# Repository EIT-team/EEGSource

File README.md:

# EEGSource
Generate EEG signals for saline phantoms

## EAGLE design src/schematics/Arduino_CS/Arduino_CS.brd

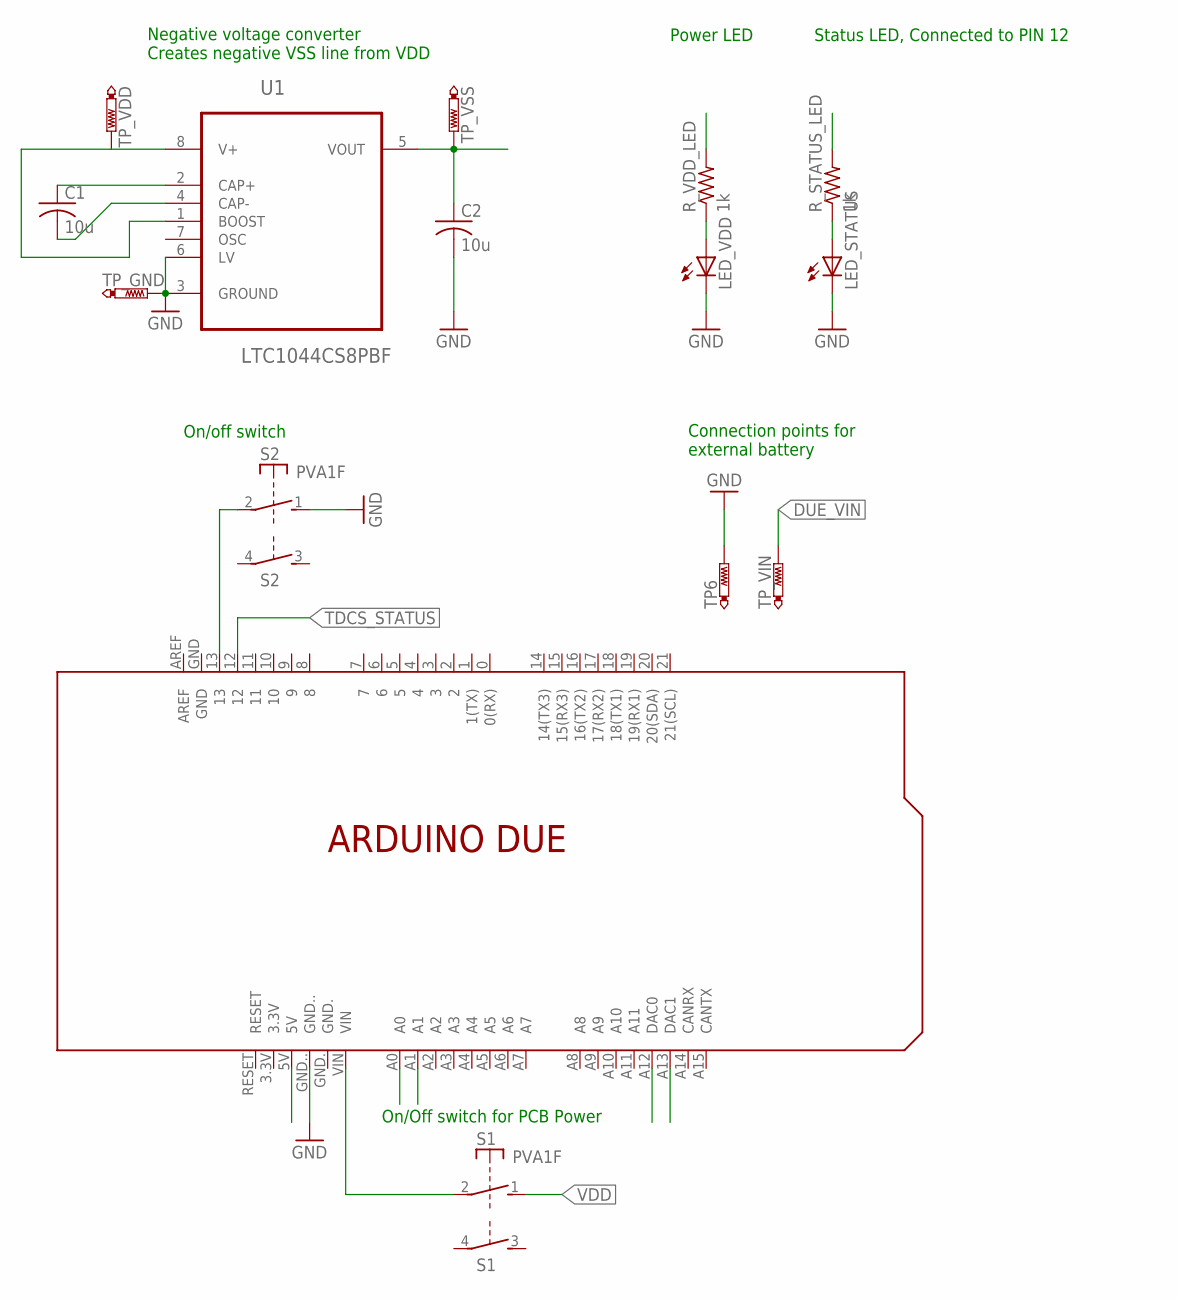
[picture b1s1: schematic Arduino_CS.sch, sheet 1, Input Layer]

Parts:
C1, C2: 10u; C0805
LED_STATUS: LEDSML0805; SML0805
LED_VDD: LEDSML0805; SML0805
PCB1: ARDUINO_DUE
R_STATUS_LED: 1k; M0805
R_VDD_LED: 1k; M0805
S1, S2: PVA1F
TP6: PTR1PAD1-13; P1-13
TP_GND: PTR1PAD1-13; P1-13
TP_VDD: PTR1PAD1-13; P1-13
TP_VIN: PTR1PAD1-13; P1-13
TP_VSS: PTR1PAD1-13; P1-13
U1: LTC1044CS8PBF; SOIC127P600X175-8N

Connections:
A0: PCB1.A0; also elsewhere on the board
A1: PCB1.A1
DAC0: PCB1.A12 (DAC0); also elsewhere on the board
DAC1: PCB1.A13 (DAC1)
DUE_5V: PCB1.5V; also elsewhere on the board
DUE_VIN: PCB1.VIN, S1.2, TP_VIN.TP
GND: C2.2, LED_STATUS.C, LED_VDD.C, PCB1.GND.., S2.1 (S), TP6.TP, TP_GND.TP, U1.3 (GROUND), U1.6 (LV); also elsewhere on the board
unnamed: PCB1.13, S2.2
unnamed: C1.1, U1.2 (CAP+)
unnamed: C1.2, U1.4 (CAP-)
unnamed: LED_STATUS.A, R_STATUS_LED.1
unnamed: LED_VDD.A, R_VDD_LED.1
TDCS_STATUS: PCB1.12, R_STATUS_LED.2
VDD: R_VDD_LED.2, S1.1 (S), TP_VDD.TP, U1.1 (BOOST), U1.8 (V+); also elsewhere on the board
VSS: C2.1, TP_VSS.TP, U1.5 (VOUT); also elsewhere on the board

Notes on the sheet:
Power LED
Status LED, Connected to PIN 12
Negative voltage converter Creates negative VSS line from VDD
On/off switch
On/Off switch for PCB Power
Connection points for external battery

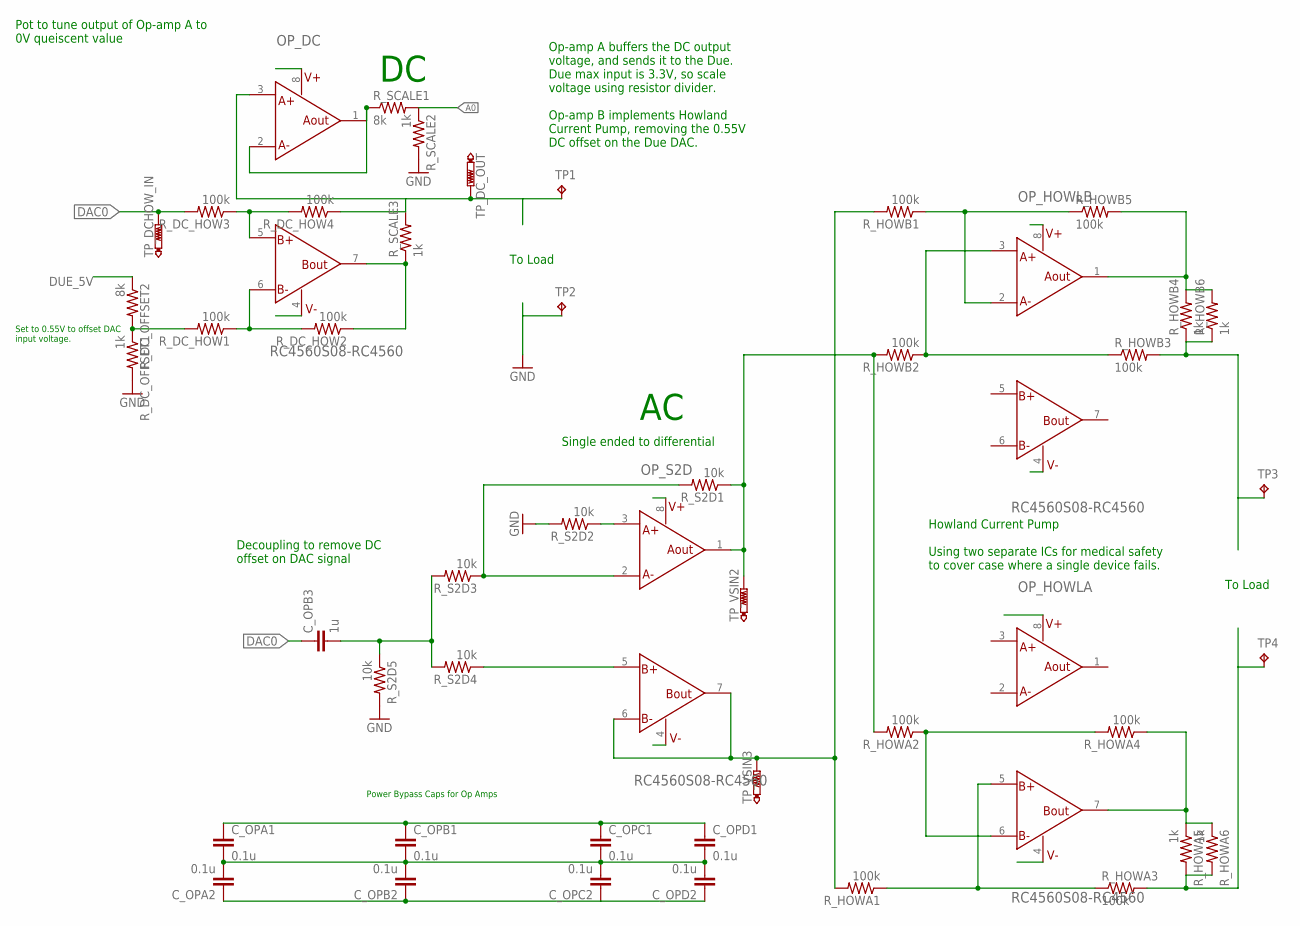
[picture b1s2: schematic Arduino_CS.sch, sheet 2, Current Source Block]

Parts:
C_OPA1, C_OPA2: 0.1u; C0805
C_OPB1, C_OPB2: 0.1u; C0805
C_OPB3: 1u; C0805
C_OPC1, C_OPC2: 0.1u; C0805
C_OPD1, C_OPD2: 0.1u; C0805
OP_DC: RC4560S08-RC4560; SO8
OP_HOWLA: RC4560S08-RC4560; SO8
OP_HOWLB: RC4560S08-RC4560; SO8
OP_S2D: RC4560S08-RC4560; SO8
R_DC_HOW1, R_DC_HOW2, R_DC_HOW3, R_DC_HOW4: 100k; R0805
R_DC_OFFSET1: 1k; R0805
R_DC_OFFSET2: 8k; R0805
R_HOWA1, R_HOWA2, R_HOWA3, R_HOWA4: 100k; R0805
R_HOWA5, R_HOWA6: 1k; R0805
R_HOWB1, R_HOWB2, R_HOWB3, R_HOWB5: 100k; R0805
R_HOWB4, R_HOWB6: 1k; R0805
R_S2D1, R_S2D2, R_S2D3, R_S2D4, R_S2D5: 10k; R0805
R_SCALE1: 8k; R0805
R_SCALE2, R_SCALE3: 1k; R0805
TP1, TP2, TP3, TP4: TPPAD1-20; P1-20
TP_DCHOW_IN: PTR1PAD1-13; P1-13
TP_DC_OUT: PTR1PAD1-13; P1-13
TP_VSIN2, TP_VSIN3: PTR1PAD1-13; P1-13

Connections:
A0: R_SCALE1.2, R_SCALE2.1; also elsewhere on the board
DAC0: C_OPB3.1, R_DC_HOW3.2, TP_DCHOW_IN.TP; also elsewhere on the board
DUE_5V: R_DC_OFFSET2.1; also elsewhere on the board
GND: C_OPA1.2, C_OPA2.2, C_OPB1.2, C_OPB2.2, C_OPC1.2, C_OPC2.2, C_OPD1.2, C_OPD2.2, R_DC_OFFSET1.2, R_S2D2.2, R_S2D5.2, R_SCALE2.2, TP2.TP; also elsewhere on the board
unnamed: OP_DC.6 (NEGB), R_DC_HOW1.1, R_DC_HOW2.2
unnamed: R_DC_HOW1.2, R_DC_OFFSET1.1, R_DC_OFFSET2.2
unnamed: C_OPB3.2, R_S2D3.2, R_S2D4.2, R_S2D5.1
unnamed: OP_S2D.6 (NEGB), OP_S2D.7 (OUTB), R_HOWA1.2, R_HOWB1.2, TP_VSIN3.TP
unnamed: OP_S2D.5 (POSB), R_S2D4.1
unnamed: OP_HOWLA.5 (POSB), R_HOWA1.1, R_HOWA3.1
unnamed: OP_S2D.1 (OUTA), R_HOWA2.2, R_HOWB2.2, R_S2D1.1, TP_VSIN2.TP
unnamed: OP_S2D.3 (POSA), R_S2D2.1
unnamed: OP_S2D.2 (NEGA), R_S2D1.2, R_S2D3.1
unnamed: OP_HOWLB.3 (POSA), R_HOWB2.1, R_HOWB3.1
unnamed: OP_HOWLB.2 (NEGA), R_HOWB1.1, R_HOWB5.1
unnamed: R_HOWB3.2, R_HOWB4.1, R_HOWB6.1, TP3.TP
unnamed: R_HOWA3.2, R_HOWA5.2, R_HOWA6.2, TP4.TP
unnamed: OP_HOWLA.7 (OUTB), R_HOWA4.1, R_HOWA5.1, R_HOWA6.1
unnamed: OP_DC.7 (OUTB), R_DC_HOW2.1, R_SCALE3.1
unnamed: OP_HOWLA.6 (NEGB), R_HOWA2.1, R_HOWA4.2
unnamed: OP_DC.1 (OUTA), OP_DC.2 (NEGA), R_SCALE1.1
unnamed: OP_HOWLB.1 (OUTA), R_HOWB4.2, R_HOWB5.2, R_HOWB6.2
unnamed: OP_DC.3 (POSA), R_DC_HOW4.1, R_SCALE3.2, TP1.TP, TP_DC_OUT.TP
unnamed: OP_DC.5 (POSB), R_DC_HOW3.1, R_DC_HOW4.2
VDD: C_OPA1.1, C_OPB1.1, C_OPC1.1, C_OPD1.1, OP_DC.8 (V+), OP_HOWLA.8 (V+), OP_HOWLB.8 (V+), OP_S2D.8 (V+); also elsewhere on the board
VSS: C_OPA2.1, C_OPB2.1, C_OPC2.1, C_OPD2.1, OP_DC.4 (V-), OP_HOWLA.4 (V-), OP_HOWLB.4 (V-), OP_S2D.4 (V-); also elsewhere on the board

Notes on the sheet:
Howland Current Pump Using two separate ICs for medical safety to cover case where a single device fails.
Power Bypass Caps for Op Amps
Single ended to differential
Pot to tune output of Op-amp A to 0V queiscent value
Decoupling to remove DC offset on DAC signal
Op-amp A buffers the DC output voltage, and sends it to the Due. Due max input is 3.3V, so scale voltage using resistor divider. Op-amp B implements Howland Current Pump, removing the 0.55V DC offset on the Due DAC.
To Load
Set to 0.55V to offset DAC input voltage.

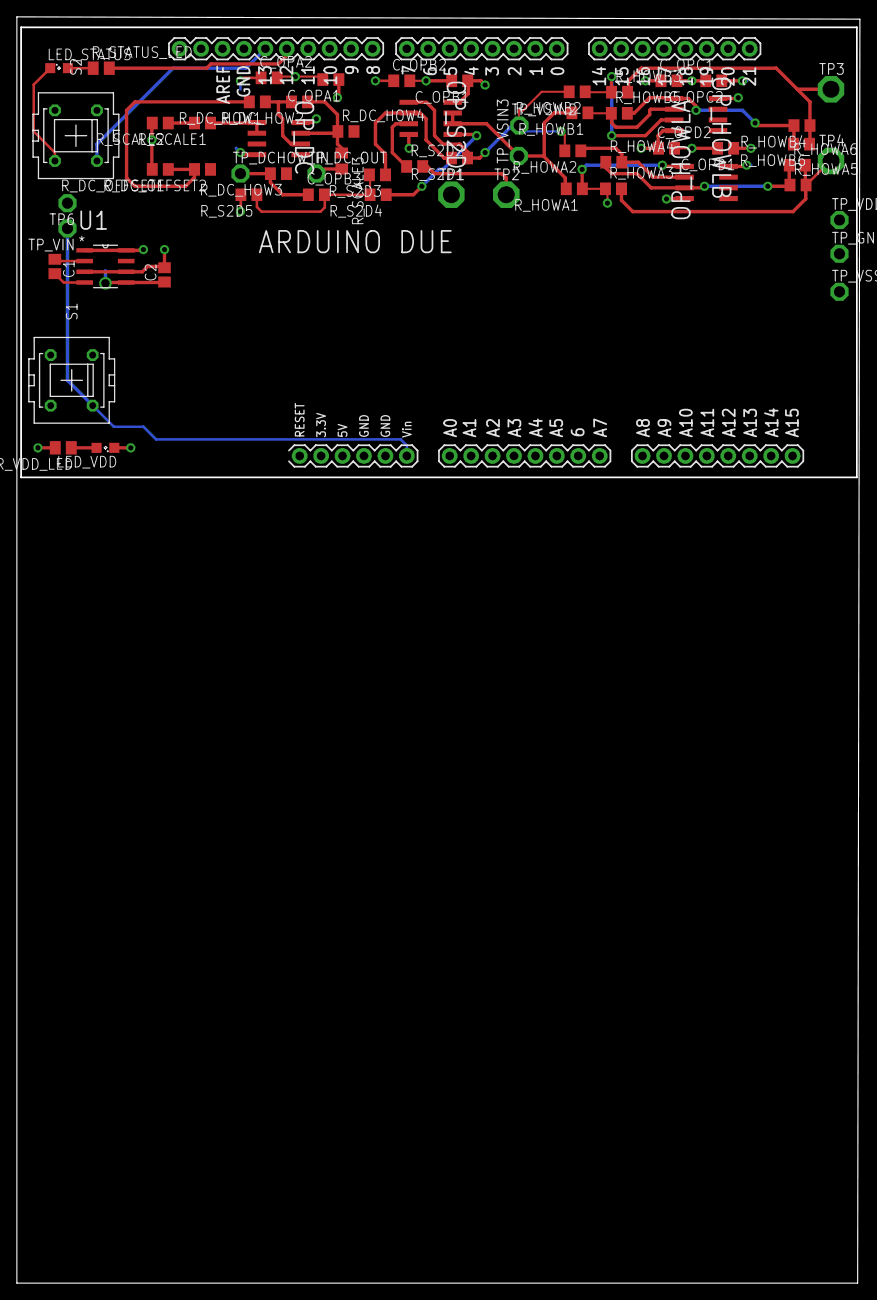
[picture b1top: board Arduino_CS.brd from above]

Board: 4 copper layers, 99.9 x 150.1 mm, 62 parts (0 on the bottom side), 33 nets.

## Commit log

2016-11-29 initial modification of example VI
2016-12-01 added better vo
2016-12-01 Added EEG gen code, and scaling of data. Switched to longer signals
2016-12-07 changed default vals
2016-12-08 testing toms bot
2016-12-14 added basic Sine Pulse generator for Arduino Due
2016-12-14 set to lowest voltage after pulse - as DC blocking not working
2016-12-14 edits to defaults on EEG out
2017-03-01 Added DDS with timer interupts on Due
2017-03-01 added Release from visual micro to gitignore
2017-03-01 fixed gitignore
2017-03-02 Pulsed Wave every Second
2017-03-06 Added repeats of pulses
2017-03-08 Added checking of padded signal, using equivalent filter
2017-06-09 Switched to 2 Hz pulses
2017-06-09 Added eeg output for dipole
2017-06-09 fixed bug in writing string for eeg wavetable
2017-07-04 Added No filter EEG signal
2017-07-04 renamed files
2017-07-20 added no filter EEG and dual eeg output
2018-11-16 comments added on laptop
2018-11-16 added arduino schematics
